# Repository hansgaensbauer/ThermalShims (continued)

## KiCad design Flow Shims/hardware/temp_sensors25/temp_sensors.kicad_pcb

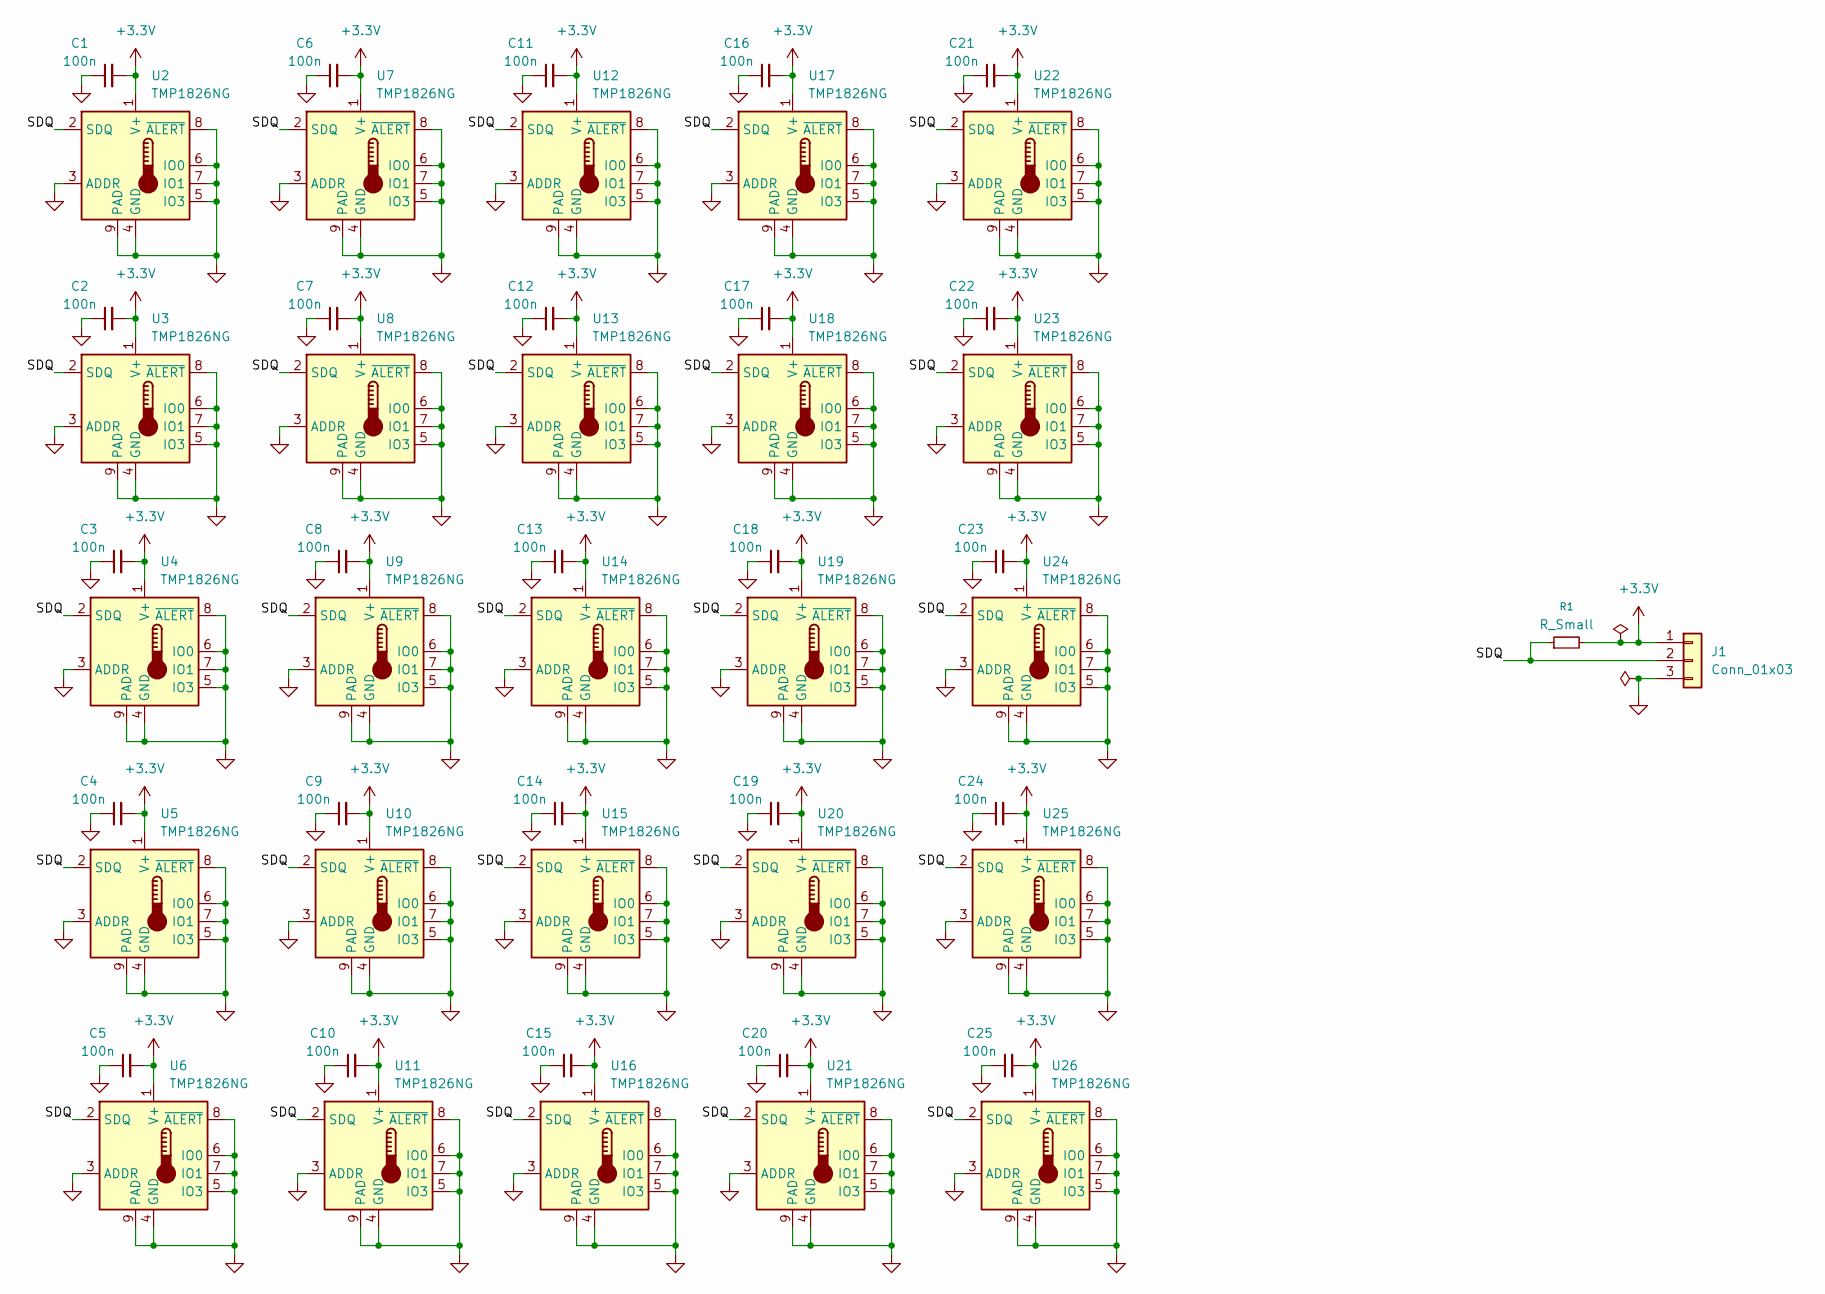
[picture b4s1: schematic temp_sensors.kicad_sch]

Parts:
C1, C2, C3, C4, C5, C6, C7, C8, C9, C10, C11, C12, C13, C14, C15, C16, C17, C18, C19, C20, C21, C22, C23, C24, C25: 100n; C_0402_1005Metric
J1: Conn_01x03; PinHeader_1x03_P1.27mm_Vertical
R1: R_Small; R_0402_1005Metric
U2, U3, U4, U5, U6, U7, U8, U9, U10, U11, U12, U13, U14, U15, U16, U17, U18, U19, U20, U21, U22, U23, U24, U25, U26: TMP1826NG; Sensirion_DFN-8-1EP_2.5x2.5mm_P0.5mm_EP1.1x1.7mm

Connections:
+3.3V: C1.2, C2.2, C3.2, C4.2, C5.2, C6.2, C7.2, C8.2, C9.2, C10.2, C11.2, C12.2, C13.2, C14.2, C15.2, C16.2, C17.2, C18.2, C19.2, C20.2, C21.2, C22.2, C23.2, C24.2, C25.2, J1.1, R1.2, U2.1 (V+), U3.1 (V+), U4.1 (V+), U5.1 (V+), U6.1 (V+), U7.1 (V+), U8.1 (V+), U9.1 (V+), U10.1 (V+), U11.1 (V+), U12.1 (V+), U13.1 (V+), U14.1 (V+), U15.1 (V+), U16.1 (V+), U17.1 (V+), U18.1 (V+), U19.1 (V+), U20.1 (V+), U21.1 (V+), U22.1 (V+), U23.1 (V+), U24.1 (V+), U25.1 (V+), U26.1 (V+)
/SDQ: J1.2, R1.1, U2.2 (SDQ), U3.2 (SDQ), U4.2 (SDQ), U5.2 (SDQ), U6.2 (SDQ), U7.2 (SDQ), U8.2 (SDQ), U9.2 (SDQ), U10.2 (SDQ), U11.2 (SDQ), U12.2 (SDQ), U13.2 (SDQ), U14.2 (SDQ), U15.2 (SDQ), U16.2 (SDQ), U17.2 (SDQ), U18.2 (SDQ), U19.2 (SDQ), U20.2 (SDQ), U21.2 (SDQ), U22.2 (SDQ), U23.2 (SDQ), U24.2 (SDQ), U25.2 (SDQ), U26.2 (SDQ)
GND: C1.1, C2.1, C3.1, C4.1, C5.1, C6.1, C7.1, C8.1, C9.1, C10.1, C11.1, C12.1, C13.1, C14.1, C15.1, C16.1, C17.1, C18.1, C19.1, C20.1, C21.1, C22.1, C23.1, C24.1, C25.1, J1.3, U2.3 (ADDR), U2.4 (GND), U2.5 (IO3), U2.6 (IO0), U2.7 (IO1), U2.8 (~ALERT), U2.9 (PAD), U3.3 (ADDR), U3.4 (GND), U3.5 (IO3), U3.6 (IO0), U3.7 (IO1), U3.8 (~ALERT), U3.9 (PAD), U4.3 (ADDR), U4.4 (GND), U4.5 (IO3), U4.6 (IO0), U4.7 (IO1), U4.8 (~ALERT), U4.9 (PAD), U5.3 (ADDR), U5.4 (GND), U5.5 (IO3), U5.6 (IO0), U5.7 (IO1), U5.8 (~ALERT), U5.9 (PAD), U6.3 (ADDR), U6.4 (GND), U6.5 (IO3), U6.6 (IO0), U6.7 (IO1), U6.8 (~ALERT), U6.9 (PAD), U7.3 (ADDR), U7.4 (GND), U7.5 (IO3), U7.6 (IO0), U7.7 (IO1), U7.8 (~ALERT), U7.9 (PAD), U8.3 (ADDR), U8.4 (GND), U8.5 (IO3), U8.6 (IO0), U8.7 (IO1), U8.8 (~ALERT), U8.9 (PAD), U9.3 (ADDR), U9.4 (GND), U9.5 (IO3), U9.6 (IO0), U9.7 (IO1), U9.8 (~ALERT), U9.9 (PAD), U10.3 (ADDR), U10.4 (GND), U10.5 (IO3), U10.6 (IO0), U10.7 (IO1), U10.8 (~ALERT), U10.9 (PAD), U11.3 (ADDR), U11.4 (GND), U11.5 (IO3), U11.6 (IO0), U11.7 (IO1), U11.8 (~ALERT), U11.9 (PAD), U12.3 (ADDR), U12.4 (GND), U12.5 (IO3), U12.6 (IO0), U12.7 (IO1), U12.8 (~ALERT), U12.9 (PAD), U13.3 (ADDR), U13.4 (GND), U13.5 (IO3), U13.6 (IO0), U13.7 (IO1), U13.8 (~ALERT), U13.9 (PAD), U14.3 (ADDR), U14.4 (GND), U14.5 (IO3), U14.6 (IO0), U14.7 (IO1), U14.8 (~ALERT), U14.9 (PAD), U15.3 (ADDR), U15.4 (GND), U15.5 (IO3), U15.6 (IO0), U15.7 (IO1), U15.8 (~ALERT), U15.9 (PAD), U16.3 (ADDR), U16.4 (GND), U16.5 (IO3), U16.6 (IO0), U16.7 (IO1), U16.8 (~ALERT), U16.9 (PAD), U17.3 (ADDR), U17.4 (GND), U17.5 (IO3), U17.6 (IO0), U17.7 (IO1), U17.8 (~ALERT), U17.9 (PAD), U18.3 (ADDR), U18.4 (GND), U18.5 (IO3), U18.6 (IO0), U18.7 (IO1), U18.8 (~ALERT), U18.9 (PAD), U19.3 (ADDR), U19.4 (GND), U19.5 (IO3), U19.6 (IO0), U19.7 (IO1), U19.8 (~ALERT), U19.9 (PAD), U20.3 (ADDR), U20.4 (GND), U20.5 (IO3), U20.6 (IO0), U20.7 (IO1), U20.8 (~ALERT), U20.9 (PAD), U21.3 (ADDR), U21.4 (GND), U21.5 (IO3), U21.6 (IO0), U21.7 (IO1), U21.8 (~ALERT), U21.9 (PAD), U22.3 (ADDR), U22.4 (GND), U22.5 (IO3), U22.6 (IO0), U22.7 (IO1), U22.8 (~ALERT), U22.9 (PAD), U23.3 (ADDR), U23.4 (GND), U23.5 (IO3), U23.6 (IO0), U23.7 (IO1), U23.8 (~ALERT), U23.9 (PAD), U24.3 (ADDR), U24.4 (GND), U24.5 (IO3), U24.6 (IO0), U24.7 (IO1), U24.8 (~ALERT), U24.9 (PAD), U25.3 (ADDR), U25.4 (GND), U25.5 (IO3), U25.6 (IO0), U25.7 (IO1), U25.8 (~ALERT), U25.9 (PAD), U26.3 (ADDR), U26.4 (GND), U26.5 (IO3), U26.6 (IO0), U26.7 (IO1), U26.8 (~ALERT), U26.9 (PAD)

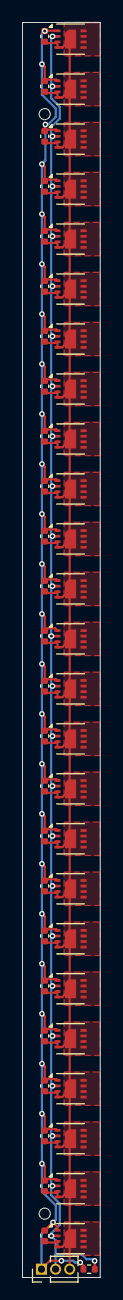
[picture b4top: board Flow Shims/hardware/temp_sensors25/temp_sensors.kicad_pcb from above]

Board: 2 copper layers, 7.0 x 113.0 mm, 52 parts (0 on the bottom side), 3 nets.

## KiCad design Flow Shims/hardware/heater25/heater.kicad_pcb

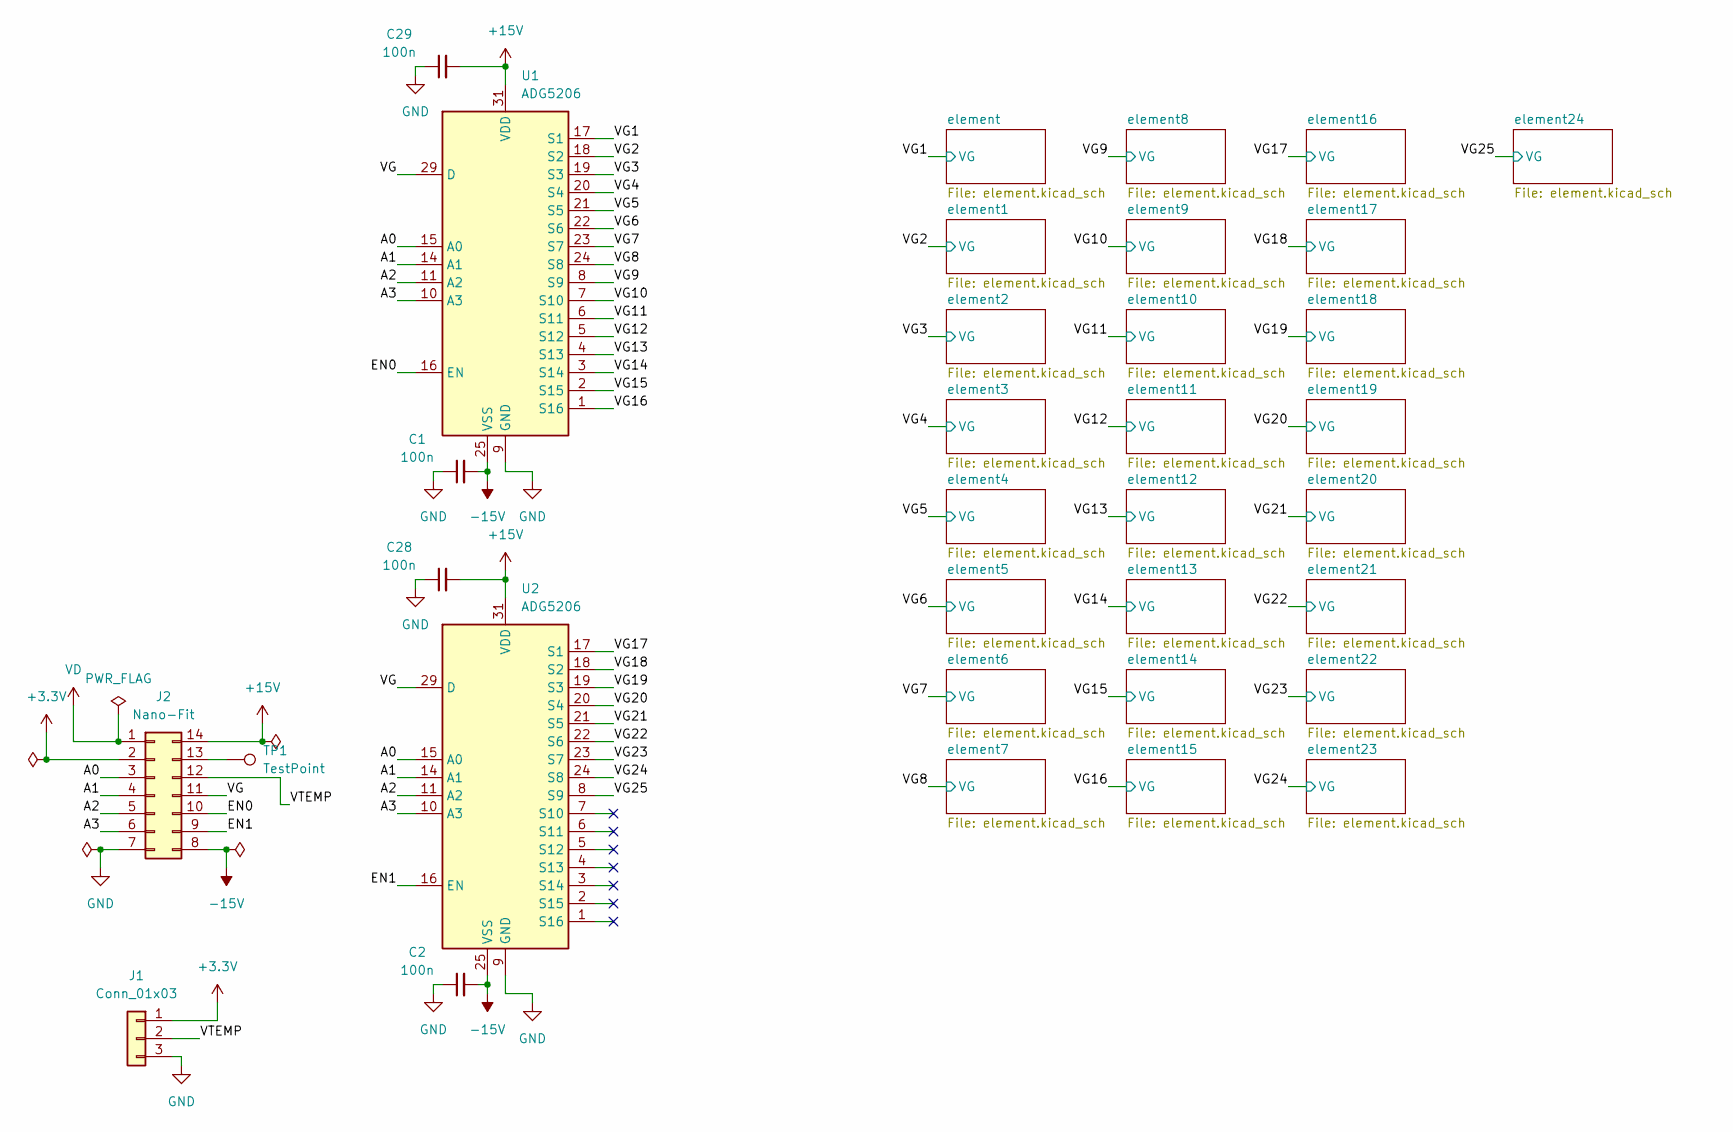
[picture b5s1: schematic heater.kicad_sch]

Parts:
C1, C2, C28, C29: 100n; C_0603_1608Metric
J1: Conn_01x03; PinHeader_1x03_P1.27mm_Vertical
J2: Nano-Fit; CONN_SD-105405-001_14_MOL
TP1: TestPoint; TestPoint_THTPad_D1.5mm_Drill0.7mm
U1, U2: ADG5206; QFN-32-1EP_5x5mm_P0.5mm_EP3.6x3.6mm

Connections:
+3.3V: J1.1, J2.2; also elsewhere on the board
+15V: C28.2, C29.2, J2.14, U1.31 (VDD), U2.31 (VDD)
-15V: C1.2, C2.2, J2.8, U1.25 (VSS), U1.33 (PAD), U2.25 (VSS), U2.33 (PAD)
/A0: J2.3, U1.15 (A0), U2.15 (A0)
/A1: J2.4, U1.14 (A1), U2.14 (A1)
/A2: J2.5, U1.11 (A2), U2.11 (A2)
/A3: J2.6, U1.10 (A3), U2.10 (A3)
/EN0: J2.10, U1.16 (EN)
/EN1: J2.9, U2.16 (EN)
/VG: J2.11, U1.29 (D), U2.29 (D)
/VG1: U1.17 (S1); also elsewhere on the board
/VG2: U1.18 (S2); also elsewhere on the board
/VG3: U1.19 (S3); also elsewhere on the board
/VG4: U1.20 (S4); also elsewhere on the board
/VG5: U1.21 (S5); also elsewhere on the board
/VG6: U1.22 (S6); also elsewhere on the board
/VG7: U1.23 (S7); also elsewhere on the board
/VG8: U1.24 (S8); also elsewhere on the board
/VG9: U1.8 (S9); also elsewhere on the board
/VG10: U1.7 (S10); also elsewhere on the board
/VG11: U1.6 (S11); also elsewhere on the board
/VG12: U1.5 (S12); also elsewhere on the board
/VG13: U1.4 (S13); also elsewhere on the board
/VG14: U1.3 (S14); also elsewhere on the board
/VG15: U1.2 (S15); also elsewhere on the board
/VG16: U1.1 (S16); also elsewhere on the board
/VG17: U2.17 (S1); also elsewhere on the board
/VG18: U2.18 (S2); also elsewhere on the board
/VG19: U2.19 (S3); also elsewhere on the board
/VG20: U2.20 (S4); also elsewhere on the board
/VG21: U2.21 (S5); also elsewhere on the board
/VG22: U2.22 (S6); also elsewhere on the board
/VG23: U2.23 (S7); also elsewhere on the board
/VG24: U2.24 (S8); also elsewhere on the board
/VG25: U2.8 (S9); also elsewhere on the board
/VTEMP: J1.2, J2.12
GND: C1.1, C2.1, C28.1, C29.1, J1.3, J2.7, U1.9 (GND), U2.9 (GND); also elsewhere on the board
unnamed: J2.13, TP1.1 (1_1)
VD: J2.1; also elsewhere on the board

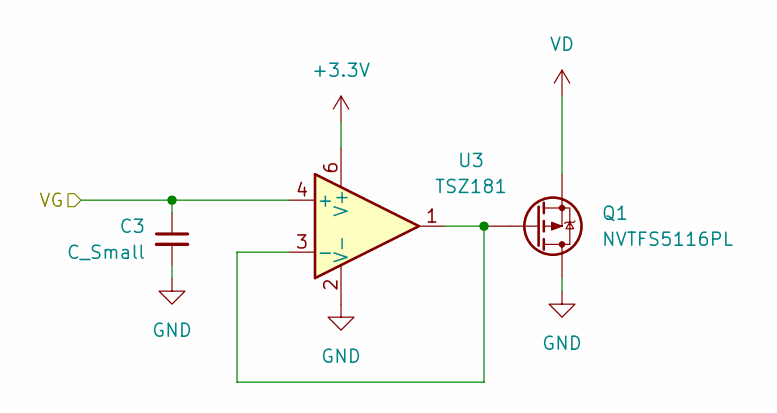
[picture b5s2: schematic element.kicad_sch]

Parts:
C3: C_Small; C_0603_1608Metric
Q1: NVTFS5116PL; WDFN8_511AB_ONS_OSI
U3: TSZ181; DFN-6_1.3x1.2mm_P0.4mm-narrow

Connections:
+3.3V: U3.6 (V+); also elsewhere on the board
/VG1: C3.1, U3.4 (+); also elsewhere on the board
GND: C3.2, Q1.5, Q1.6, Q1.7, Q1.8, U3.2 (V-); also elsewhere on the board
unnamed: Q1.4, U3.1, U3.3 (-)
VD: Q1.1, Q1.2, Q1.3; also elsewhere on the board

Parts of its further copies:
C4, C5, C6, C7, C8, C9, C10, C11, C12, C13, C14, C15, C16, C17, C18, C19, C20, C21, C22, C23, C24, C25, C26, C27: C_Small; C_0603_1608Metric
Q2, Q3, Q4, Q5, Q6, Q7, Q8, Q9, Q10, Q11, Q12, Q13, Q14, Q15, Q16, Q17, Q18, Q19, Q20, Q21, Q22, Q23, Q24, Q25: NVTFS5116PL; WDFN8_511AB_ONS_OSI
U4, U5, U6, U7, U8, U9, U10, U11, U12, U13, U14, U15, U16, U17, U18, U19, U20, U21, U22, U23, U24, U25, U26, U27: TSZ181; DFN-6_1.3x1.2mm_P0.4mm-narrow

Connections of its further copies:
+3.3V: U4.6 (V+), U5.6 (V+), U6.6 (V+), U7.6 (V+), U8.6 (V+), U9.6 (V+), U10.6 (V+), U11.6 (V+), U12.6 (V+), U13.6 (V+), U14.6 (V+), U15.6 (V+), U16.6 (V+), U17.6 (V+), U18.6 (V+), U19.6 (V+), U20.6 (V+), U21.6 (V+), U22.6 (V+), U23.6 (V+), U24.6 (V+), U25.6 (V+), U26.6 (V+), U27.6 (V+); also elsewhere on the board
/VG2: C4.1, U4.4 (+); also elsewhere on the board
/VG3: C5.1, U5.4 (+); also elsewhere on the board
/VG4: C6.1, U6.4 (+); also elsewhere on the board
/VG5: C7.1, U7.4 (+); also elsewhere on the board
/VG6: C8.1, U8.4 (+); also elsewhere on the board
/VG7: C9.1, U9.4 (+); also elsewhere on the board
/VG8: C10.1, U10.4 (+); also elsewhere on the board
/VG9: C11.1, U11.4 (+); also elsewhere on the board
/VG10: C12.1, U12.4 (+); also elsewhere on the board
/VG11: C13.1, U13.4 (+); also elsewhere on the board
/VG12: C14.1, U14.4 (+); also elsewhere on the board
/VG13: C15.1, U15.4 (+); also elsewhere on the board
/VG14: C16.1, U16.4 (+); also elsewhere on the board
/VG15: C17.1, U17.4 (+); also elsewhere on the board
/VG16: C18.1, U18.4 (+); also elsewhere on the board
/VG17: C19.1, U19.4 (+); also elsewhere on the board
/VG18: C20.1, U20.4 (+); also elsewhere on the board
/VG19: C21.1, U21.4 (+); also elsewhere on the board
/VG20: C22.1, U22.4 (+); also elsewhere on the board
/VG21: C23.1, U23.4 (+); also elsewhere on the board
/VG22: C24.1, U24.4 (+); also elsewhere on the board
/VG23: C25.1, U25.4 (+); also elsewhere on the board
/VG24: C26.1, U26.4 (+); also elsewhere on the board
/VG25: C27.1, U27.4 (+); also elsewhere on the board
GND: C4.2, C5.2, C6.2, C7.2, C8.2, C9.2, C10.2, C11.2, C12.2, C13.2, C14.2, C15.2, C16.2, C17.2, C18.2, C19.2, C20.2, C21.2, C22.2, C23.2, C24.2, C25.2, C26.2, C27.2, Q2.5, Q2.6, Q2.7, Q2.8, Q3.5, Q3.6, Q3.7, Q3.8, Q4.5, Q4.6, Q4.7, Q4.8, Q5.5, Q5.6, Q5.7, Q5.8, Q6.5, Q6.6, Q6.7, Q6.8, Q7.5, Q7.6, Q7.7, Q7.8, Q8.5, Q8.6, Q8.7, Q8.8, Q9.5, Q9.6, Q9.7, Q9.8, Q10.5, Q10.6, Q10.7, Q10.8, Q11.5, Q11.6, Q11.7, Q11.8, Q12.5, Q12.6, Q12.7, Q12.8, Q13.5, Q13.6, Q13.7, Q13.8, Q14.5, Q14.6, Q14.7, Q14.8, Q15.5, Q15.6, Q15.7, Q15.8, Q16.5, Q16.6, Q16.7, Q16.8, Q17.5, Q17.6, Q17.7, Q17.8, Q18.5, Q18.6, Q18.7, Q18.8, Q19.5, Q19.6, Q19.7, Q19.8, Q20.5, Q20.6, Q20.7, Q20.8, Q21.5, Q21.6, Q21.7, Q21.8, Q22.5, Q22.6, Q22.7, Q22.8, Q23.5, Q23.6, Q23.7, Q23.8, Q24.5, Q24.6, Q24.7, Q24.8, Q25.5, Q25.6, Q25.7, Q25.8, U4.2 (V-), U5.2 (V-), U6.2 (V-), U7.2 (V-), U8.2 (V-), U9.2 (V-), U10.2 (V-), U11.2 (V-), U12.2 (V-), U13.2 (V-), U14.2 (V-), U15.2 (V-), U16.2 (V-), U17.2 (V-), U18.2 (V-), U19.2 (V-), U20.2 (V-), U21.2 (V-), U22.2 (V-), U23.2 (V-), U24.2 (V-), U25.2 (V-), U26.2 (V-), U27.2 (V-); also elsewhere on the board
unnamed: Q2.4, U4.1, U4.3 (-)
unnamed: Q3.4, U5.1, U5.3 (-)
unnamed: Q4.4, U6.1, U6.3 (-)
unnamed: Q5.4, U7.1, U7.3 (-)
unnamed: Q6.4, U8.1, U8.3 (-)
unnamed: Q7.4, U9.1, U9.3 (-)
unnamed: Q8.4, U10.1, U10.3 (-)
unnamed: Q9.4, U11.1, U11.3 (-)
unnamed: Q10.4, U12.1, U12.3 (-)
unnamed: Q11.4, U13.1, U13.3 (-)
unnamed: Q12.4, U14.1, U14.3 (-)
unnamed: Q13.4, U15.1, U15.3 (-)
unnamed: Q14.4, U16.1, U16.3 (-)
unnamed: Q15.4, U17.1, U17.3 (-)
unnamed: Q16.4, U18.1, U18.3 (-)
unnamed: Q17.4, U19.1, U19.3 (-)
unnamed: Q18.4, U20.1, U20.3 (-)
unnamed: Q19.4, U21.1, U21.3 (-)
unnamed: Q20.4, U22.1, U22.3 (-)
unnamed: Q21.4, U23.1, U23.3 (-)
unnamed: Q22.4, U24.1, U24.3 (-)
unnamed: Q23.4, U25.1, U25.3 (-)
unnamed: Q24.4, U26.1, U26.3 (-)
unnamed: Q25.4, U27.1, U27.3 (-)
VD: Q2.1, Q2.2, Q2.3, Q3.1, Q3.2, Q3.3, Q4.1, Q4.2, Q4.3, Q5.1, Q5.2, Q5.3, Q6.1, Q6.2, Q6.3, Q7.1, Q7.2, Q7.3, Q8.1, Q8.2, Q8.3, Q9.1, Q9.2, Q9.3, Q10.1, Q10.2, Q10.3, Q11.1, Q11.2, Q11.3, Q12.1, Q12.2, Q12.3, Q13.1, Q13.2, Q13.3, Q14.1, Q14.2, Q14.3, Q15.1, Q15.2, Q15.3, Q16.1, Q16.2, Q16.3, Q17.1, Q17.2, Q17.3, Q18.1, Q18.2, Q18.3, Q19.1, Q19.2, Q19.3, Q20.1, Q20.2, Q20.3, Q21.1, Q21.2, Q21.3, Q22.1, Q22.2, Q22.3, Q23.1, Q23.2, Q23.3, Q24.1, Q24.2, Q24.3, Q25.1, Q25.2, Q25.3; also elsewhere on the board

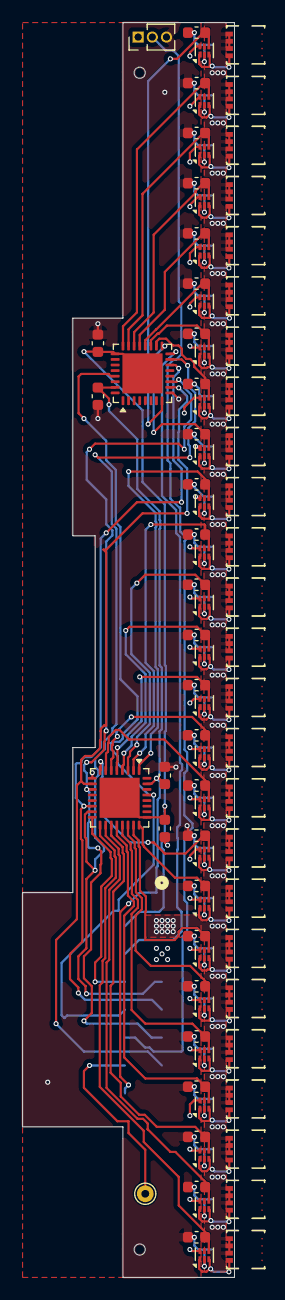
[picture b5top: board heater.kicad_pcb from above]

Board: 4 copper layers, 19.0 x 112.5 mm, 84 parts (1 on the bottom side), 64 nets.

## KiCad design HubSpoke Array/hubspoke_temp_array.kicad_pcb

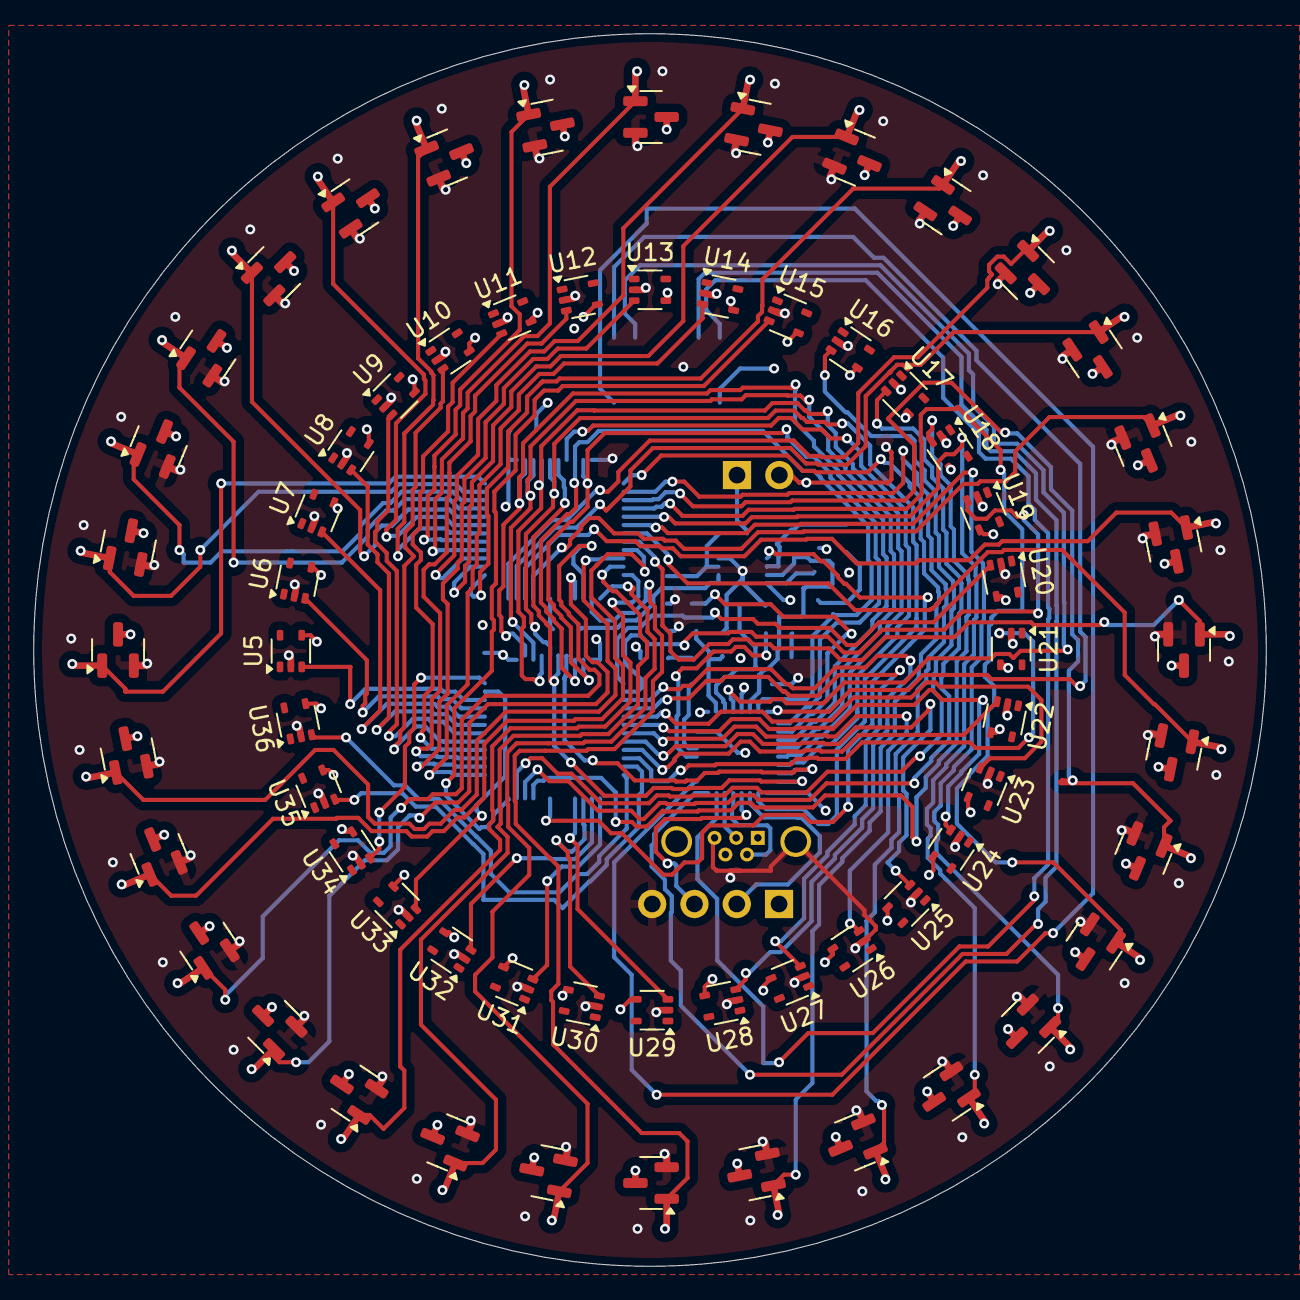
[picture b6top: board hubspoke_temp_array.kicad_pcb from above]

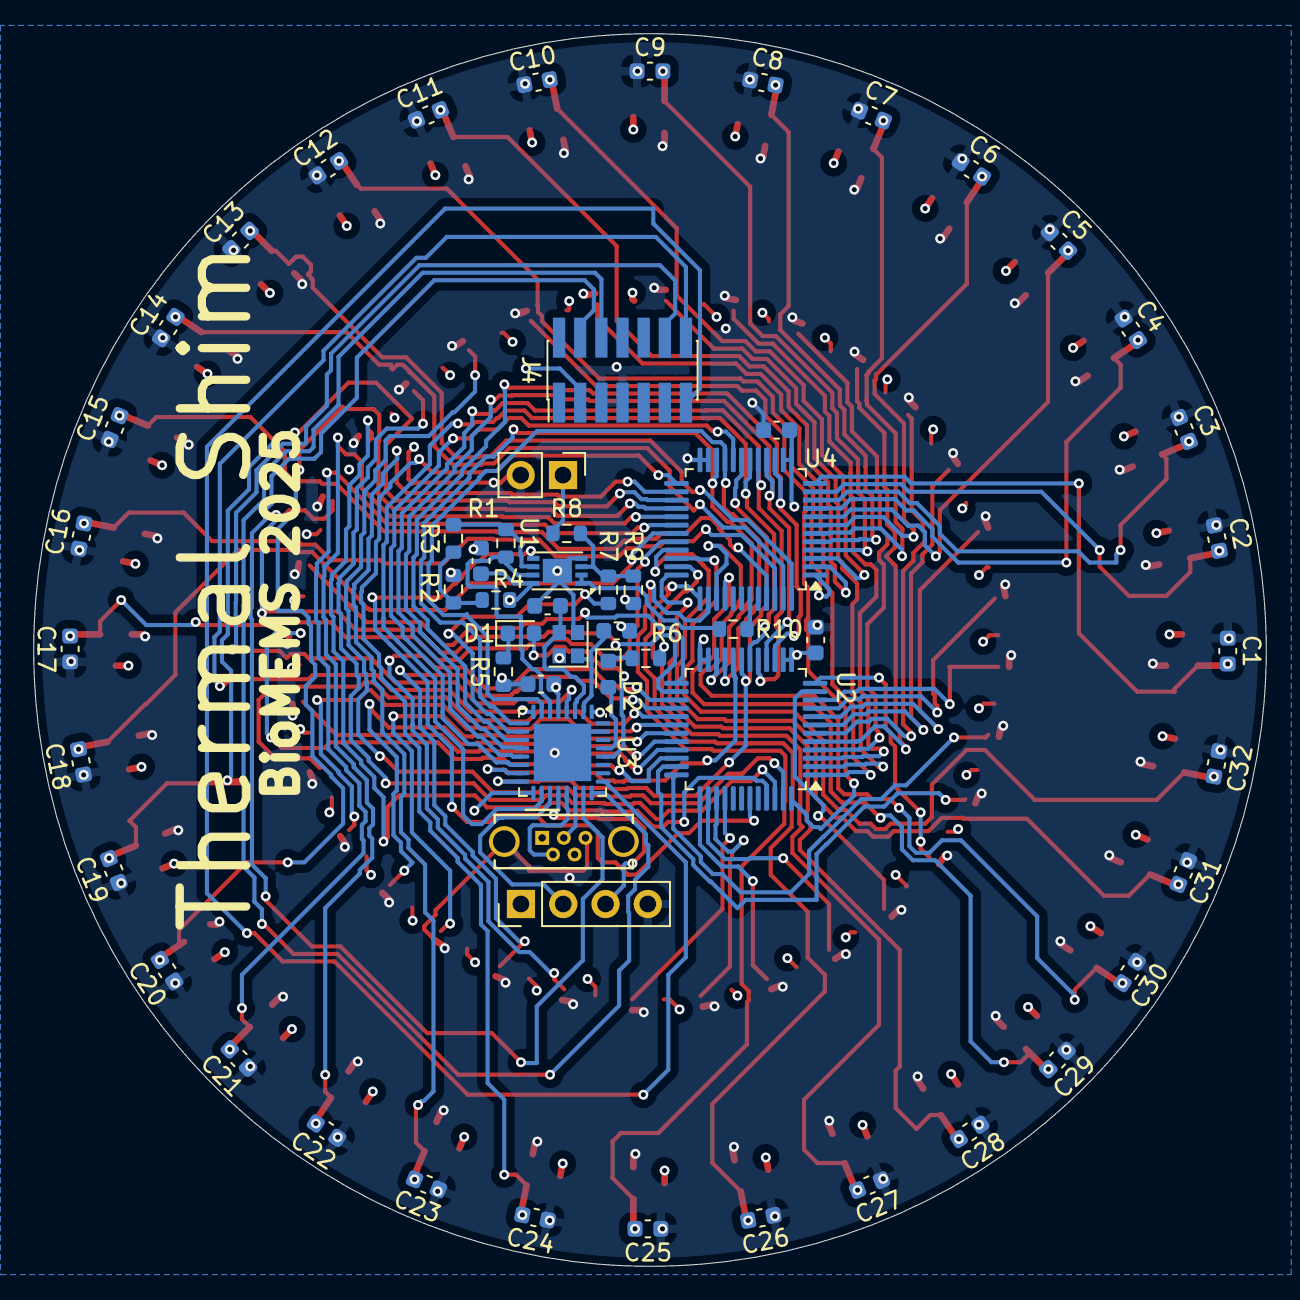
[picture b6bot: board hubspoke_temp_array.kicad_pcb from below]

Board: 4 copper layers, 74.0 x 74.0 mm, 123 parts (59 on the bottom side), 98 nets.

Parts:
C1, C2, C3, C4, C5, C6, C7, C8, C9, C10, C11, C12, C13, C14, C15, C16, C17, C18, C19, C20, C21, C22, C23, C24, C25, C26, C27, C28, C29, C30, C31, C32, C35, C36, C37, C38: 100n; C_0603_1608Metric
C33, C34: 10p; C_0603_1608Metric
D1, D2: LED_Small; LED_0603_1608Metric
J1: Conn_01x02_Pin; PinHeader_1x02_P2.54mm_Vertical
J2: Conn_01x04_Pin; PinHeader_1x04_P2.54mm_Vertical
J3: USB_B_Micro; USB_Micro-B_Wuerth_614105150721_Vertical_CircularHoles
J4: Conn_02x07_Odd_Even; PinHeader_2x07_P1.27mm_Vertical_SMD
Q1, Q2, Q3, Q4, Q5, Q6, Q7, Q8, Q9, Q10, Q11, Q12, Q13, Q14, Q15, Q16, Q17, Q18, Q19, Q20, Q21, Q22, Q23, Q24, Q25, Q26, Q27, Q28, Q29, Q30, Q31, Q32: BSS123NH6327XTSA1; SOT-23
R1, R2, R3, R4, R5, R6, R7, R8, R9, R10: R_Small; R_0603_1608Metric
U1: MCP6002-xMC; DFN-8-1EP_3x2mm_P0.5mm_EP1.75x1.45mm
U2, U4: ADG732; TQFP-48_7x7mm_P0.5mm
U3: STM32L052K8Ux; QFN-32-1EP_5x5mm_P0.5mm_EP3.45x3.45mm
U5, U6, U7, U8, U9, U10, U11, U12, U13, U14, U15, U16, U17, U18, U19, U20, U21, U22, U23, U24, U25, U26, U27, U28, U29, U30, U31, U32, U33, U34, U35, U36: MCP9700Ax-ELT; SOT-353_SC-70-5
Y1: Crystal_GND24; Crystal_SMD_2016-4Pin_2.0x1.6mm

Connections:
+3.3V: C35.1, C36.1, C37.1, C38.2, J1.1, J2.1, J4.3, Q1.3 (D), Q2.3 (D), Q3.3 (D), Q4.3 (D), Q5.3 (D), Q6.3 (D), Q7.3 (D), Q8.3 (D), Q9.3 (D), Q10.3 (D), Q11.3 (D), Q12.3 (D), Q13.3 (D), Q14.3 (D), Q15.3 (D), Q16.3 (D), Q17.3 (D), Q18.3 (D), Q19.3 (D), Q20.3 (D), Q21.3 (D), Q22.3 (D), Q23.3 (D), Q24.3 (D), Q25.3 (D), Q26.3 (D), Q27.3 (D), Q28.3 (D), Q29.3 (D), Q30.3 (D), Q31.3 (D), Q32.3 (D), R4.1, R8.2, U1.8 (V+), U2.13 (VDD), U2.14 (VDD), U3.1 (VDD), U3.5 (VDDA), U3.17 (VDD), U4.13 (VDD), U4.14 (VDD), U5.4 (V_{DD}), U6.4 (V_{DD}), U7.4 (V_{DD}), U8.4 (V_{DD}), U9.4 (V_{DD}), U10.4 (V_{DD}), U11.4 (V_{DD}), U12.4 (V_{DD}), U13.4 (V_{DD}), U14.4 (V_{DD}), U15.4 (V_{DD}), U16.4 (V_{DD}), U17.4 (V_{DD}), U18.4 (V_{DD}), U19.4 (V_{DD}), U20.4 (V_{DD}), U21.4 (V_{DD}), U22.4 (V_{DD}), U23.4 (V_{DD}), U24.4 (V_{DD}), U25.4 (V_{DD}), U26.4 (V_{DD}), U27.4 (V_{DD}), U28.4 (V_{DD}), U29.4 (V_{DD}), U30.4 (V_{DD}), U31.4 (V_{DD}), U32.4 (V_{DD}), U33.4 (V_{DD}), U34.4 (V_{DD}), U35.4 (V_{DD}), U36.4 (V_{DD})
/A0: U2.15 (A0), U3.11 (PA5), U4.15 (A0)
/A1: U2.16 (A1), U3.12 (PA6), U4.16 (A1)
/A2: U2.17 (A2), U3.13 (PA7), U4.17 (A2)
/A3: U2.18 (A3), U3.18 (PA8), U4.18 (A3)
/A4: U2.19 (A4), U3.16 (PB2), U4.19 (A4)
/CS_DRIVE: U3.14 (PB0), U4.20 (~CS)
/CS_TEMP: U2.20 (~CS), U3.15 (PB1)
/DAC: R7.2, U3.10 (PA4)
/EN: U2.22 (~EN), U3.9 (PA3), U4.22 (~EN)
/G1: C1.2, Q1.1 (G), U4.12 (S1)
/G2: C2.2, Q2.1 (G), U4.11 (S2)
/G3: C3.2, Q3.1 (G), U4.10 (S3)
/G4: C4.2, Q4.1 (G), U4.9 (S4)
/G5: C5.2, Q5.1 (G), U4.8 (S5)
/G6: C6.2, Q6.1 (G), U4.7 (S6)
/G7: C7.2, Q7.1 (G), U4.6 (S7)
/G8: C8.2, Q8.1 (G), U4.5 (S8)
/G9: C9.2, Q9.1 (G), U4.4 (S9)
/G10: C10.2, Q10.1 (G), U4.3 (S10)
/G11: C11.2, Q11.1 (G), U4.2 (S11)
/G12: C12.2, Q12.1 (G), U4.1 (S12)
/G13: C13.2, Q13.1 (G), U4.48 (S13)
/G14: C14.2, Q14.1 (G), U4.47 (S14)
/G15: C16.2, Q16.1 (G), U4.46 (S15)
/G16: C15.2, Q15.1 (G), U4.45 (S16)
/G17: C24.2, Q24.1 (G), U4.25 (S17)
/G18: C23.2, Q23.1 (G), U4.26 (S18)
/G19: C19.2, Q19.1 (G), U4.27 (S19)
/G20: C20.2, Q20.1 (G), U4.28 (S20)
/G21: C22.2, Q22.1 (G), U4.29 (S21)
/G22: C21.2, Q21.1 (G), U4.30 (S22)
/G23: C18.2, Q18.1 (G), U4.31 (S23)
/G24: C17.2, Q17.1 (G), U4.32 (S24)
/G25: C31.2, Q31.1 (G), U4.33 (S25)
/G26: C32.2, Q32.1 (G), U4.34 (S26)
/G27: C27.2, Q27.1 (G), U4.35 (S27)
/G28: C28.2, Q28.1 (G), U4.36 (S28)
/G29: C26.2, Q26.1 (G), U4.37 (S29)
/G30: C25.2, Q25.1 (G), U4.38 (S30)
/G31: C30.2, Q30.1 (G), U4.39 (S31)
/G32: C29.2, Q29.1 (G), U4.40 (S32)
/RX: J2.3, U3.20 (PA10)
/RX2: J4.13, U3.25 (PA15)
/SWCLK: J4.6, U3.24 (PA14)
/SWDIO: J4.4, U3.23 (PA13)
/TEMP: R1.2, U1.7, U3.6 (PA0)
/TH1: U2.10 (S3), U5.3 (V_{OUT})
/TH2: U2.9 (S4), U6.3 (V_{OUT})
/TH3: U2.8 (S5), U7.3 (V_{OUT})
/TH4: U2.7 (S6), U8.3 (V_{OUT})
/TH5: U2.6 (S7), U9.3 (V_{OUT})
/TH6: U2.5 (S8), U10.3 (V_{OUT})
/TH7: U2.4 (S9), U11.3 (V_{OUT})
/TH8: U2.3 (S10), U12.3 (V_{OUT})
/TH9: U2.2 (S11), U13.3 (V_{OUT})
/TH10: U2.1 (S12), U14.3 (V_{OUT})
/TH11: U2.48 (S13), U15.3 (V_{OUT})
/TH12: U2.47 (S14), U16.3 (V_{OUT})
/TH13: U2.46 (S15), U17.3 (V_{OUT})
/TH14: U2.45 (S16), U18.3 (V_{OUT})
/TH15: U2.25 (S17), U20.3 (V_{OUT})
/TH16: U2.26 (S18), U19.3 (V_{OUT})
/TH17: U2.27 (S19), U28.3 (V_{OUT})
/TH18: U2.28 (S20), U27.3 (V_{OUT})
/TH19: U2.29 (S21), U23.3 (V_{OUT})
/TH20: U2.30 (S22), U24.3 (V_{OUT})
/TH21: U2.31 (S23), U26.3 (V_{OUT})
/TH22: U2.32 (S24), U25.3 (V_{OUT})
/TH23: U2.33 (S25), U22.3 (V_{OUT})
/TH24: U2.34 (S26), U21.3 (V_{OUT})
/TH25: U2.35 (S27), U35.3 (V_{OUT})
/TH26: U2.36 (S28), U36.3 (V_{OUT})
/TH27: U2.37 (S29), U31.3 (V_{OUT})
/TH28: U2.38 (S30), U32.3 (V_{OUT})
/TH29: U2.39 (S31), U30.3 (V_{OUT})
/TH30: U2.40 (S32), U29.3 (V_{OUT})
/TH31: U2.12 (S1), U34.3 (V_{OUT})
/TH32: U2.11 (S2), U33.3 (V_{OUT})
/TX: J2.2, U3.19 (PA9)
/TX2: J4.14, U3.8 (PA2)
/USB_DM: J3.2 (D-), U3.21 (PA11)
/USB_DP: J3.3 (D+), U3.22 (PA12)
/WR: U2.21 (~WR), U3.7 (PA1), U4.21 (~WR)
/~RST: J4.12, U3.4 (NRST)
GND: C1.1, C2.1, C3.1, C4.1, C5.1, C6.1, C7.1, C8.1, C9.1, C10.1, C11.1, C12.1, C13.1, C14.1, C15.1, C16.1, C17.1, C18.1, C19.1, C20.1, C21.1, C22.1, C23.1, C24.1, C25.1, C26.1, C27.1, C28.1, C29.1, C30.1, C31.1, C32.1, C33.1, C34.1, C35.2, C36.2, C37.2, C38.1, J1.2, J2.4, J3.5 (GND), J3.6 (Shield), J4.5, J4.7, Q1.2 (S), Q2.2 (S), Q3.2 (S), Q4.2 (S), Q5.2 (S), Q6.2 (S), Q7.2 (S), Q8.2 (S), Q9.2 (S), Q10.2 (S), Q11.2 (S), Q12.2 (S), Q13.2 (S), Q14.2 (S), Q15.2 (S), Q16.2 (S), Q17.2 (S), Q18.2 (S), Q19.2 (S), Q20.2 (S), Q21.2 (S), Q22.2 (S), Q23.2 (S), Q24.2 (S), Q25.2 (S), Q26.2 (S), Q27.2 (S), Q28.2 (S), Q29.2 (S), Q30.2 (S), Q31.2 (S), Q32.2 (S), R2.1, R5.1, R6.1, R9.1, U1.4 (V-), U1.9 (V-), U2.23 (GND), U2.24 (VSS), U3.31 (BOOT0), U3.33 (VSS), U4.23 (GND), U4.24 (VSS), U5.2 (GND), U6.2 (GND), U7.2 (GND), U8.2 (GND), U9.2 (GND), U10.2 (GND), U11.2 (GND), U12.2 (GND), U13.2 (GND), U14.2 (GND), U15.2 (GND), U16.2 (GND), U17.2 (GND), U18.2 (GND), U19.2 (GND), U20.2 (GND), U21.2 (GND), U22.2 (GND), U23.2 (GND), U24.2 (GND), U25.2 (GND), U26.2 (GND), U27.2 (GND), U28.2 (GND), U29.2 (GND), U30.2 (GND), U31.2 (GND), U32.2 (GND), U33.2 (GND), U34.2 (GND), U35.2 (GND), U36.2 (GND), Y1.2, Y1.4
unnamed: D1.2 (A), U3.28 (PB5)
unnamed: D1.1 (K), R5.2
unnamed: D2.2 (A), U3.29 (PB6)
unnamed: D2.1 (K), R6.2
unnamed: R2.2, R3.1, R4.2
unnamed: R7.1, R8.1, R9.2, U1.3 (+)
unnamed: R10.1, U1.1, U1.2 (-)
unnamed: U1.5 (+), U2.43 (D)
unnamed: R1.1, R3.2, U1.6 (-)
unnamed: C34.2, U3.2 (PC14), Y1.1
unnamed: C33.2, U3.3 (PC15), Y1.3
unnamed: R10.2, U4.43 (D)

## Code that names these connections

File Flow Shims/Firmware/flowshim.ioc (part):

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Mcu.Name=STM32L052K(6-8)Ux
Mcu.Package=UFQFPN32
Mcu.UserName=STM32L052K8Ux
PA1.GPIOParameters=GPIO_Label
PA1.GPIO_Label=A1
PA1.Signal=GPIO_Output
PA10.GPIOParameters=GPIO_Label
PA10.GPIO_Label=EN1_0
PA10.Signal=GPIO_Output
PA11.Mode=Device
PA11.Signal=USB_DM
PA12.Mode=Device
PA12.Signal=USB_DP
PA3.GPIOParameters=GPIO_Label
PA3.GPIO_Label=A0
PA3.Signal=GPIO_Output
PA4.Signal=COMP_DAC1_group
PA5.GPIOParameters=GPIO_Label
PA5.GPIO_Label=A2
PA5.Signal=GPIO_Output
PA6.GPIOParameters=GPIO_Label
PA6.GPIO_Label=A3
PA6.Signal=GPIO_Output
PA7.GPIOParameters=GPIO_Label
PA7.GPIO_Label=VD_EN
PA7.Signal=GPIO_Output
PA8.GPIOParameters=GPIO_Label
PA8.GPIO_Label=EN0_0
PA8.Signal=GPIO_Output
PA9.GPIOParameters=PinState,GPIO_PuPd,GPIO_Label,GPIO_ModeDefaultOutputPP
PA9.GPIO_Label=VTEMP
PA9.GPIO_ModeDefaultOutputPP=GPIO_MODE_OUTPUT_OD
PA9.GPIO_PuPd=GPIO_PULLUP
PA9.PinState=GPIO_PIN_SET
PA9.Signal=GPIO_Output
PB0.GPIOParameters=GPIO_Label
PB0.GPIO_Label=EN0_1
PB0.Signal=GPIO_Output
PB1.GPIOParameters=GPIO_Label
PB1.GPIO_Label=EN1_1
PB1.Signal=GPIO_Output
PB5.GPIOParameters=PinState,GPIO_Label
PB5.GPIO_Label=LED1
PB5.PinState=GPIO_PIN_RESET
PB5.Signal=GPIO_Output
PB6.GPIOParameters=GPIO_Label
PB6.GPIO_Label=LED2
PB6.Signal=GPIO_Output
RCC.SYSCLKFreq_VALUE=16000000
RCC.SYSCLKSource=RCC_SYSCLKSOURCE_HSI
board=custom

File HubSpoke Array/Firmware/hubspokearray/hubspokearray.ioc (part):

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Mcu.Name=STM32L052K(6-8)Ux
Mcu.Package=UFQFPN32
Mcu.UserName=STM32L052K8Ux
PA0.Mode=IN0
PA0.Signal=ADC_IN0
PA1.GPIOParameters=GPIO_Label
PA1.GPIO_Label=WR
PA1.Signal=GPIO_Output
PA10.Mode=Asynchronous
PA10.Signal=USART1_RX
PA15.Mode=Asynchronous
PA15.Signal=USART2_RX
PA2.Mode=Asynchronous
PA2.Signal=USART2_TX
PA3.GPIOParameters=GPIO_Label
PA3.GPIO_Label=EN
PA3.Signal=GPIO_Output
PA4.GPIOParameters=GPIO_Label
PA4.GPIO_Label=DAC
PA4.Signal=GPIO_Output
PA5.GPIOParameters=GPIO_Label
PA5.GPIO_Label=A0
PA5.Signal=GPIO_Output
PA6.GPIOParameters=GPIO_Label
PA6.GPIO_Label=A1
PA6.Signal=GPIO_Output
PA7.GPIOParameters=GPIO_Label
PA7.GPIO_Label=A2
PA7.Signal=GPIO_Output
PA8.GPIOParameters=GPIO_Label
PA8.GPIO_Label=A3
PA8.Signal=GPIO_Output
PA9.Mode=Asynchronous
PA9.Signal=USART1_TX
PB0.GPIOParameters=GPIO_Label
PB0.GPIO_Label=CS_DRIVE
PB0.Signal=GPIO_Output
PB1.GPIOParameters=GPIO_Label
PB1.GPIO_Label=CS_TEMP
PB1.Signal=GPIO_Output
PB2.GPIOParameters=GPIO_Label
PB2.GPIO_Label=A4
PB2.Signal=GPIO_Output
PB5.GPIOParameters=GPIO_Label
PB5.GPIO_Label=LD1
PB5.Signal=GPIO_Output
PB6.GPIOParameters=GPIO_Label
PB6.GPIO_Label=LD2
PB6.Signal=GPIO_Output
RCC.SYSCLKFreq_VALUE=16000000
RCC.SYSCLKSource=RCC_SYSCLKSOURCE_HSI
board=custom

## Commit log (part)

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2026-05-26 Start flow shims
2026-05-26 TS25 PCBs fit in CAD
2026-05-26 Controller DRC/ERC clean
2026-05-27 Add 17 element versions
2026-05-27 All boards DRC/ERC clean
2026-05-28 Add scanner notebooks
2026-06-23 Single function fieldmapping
